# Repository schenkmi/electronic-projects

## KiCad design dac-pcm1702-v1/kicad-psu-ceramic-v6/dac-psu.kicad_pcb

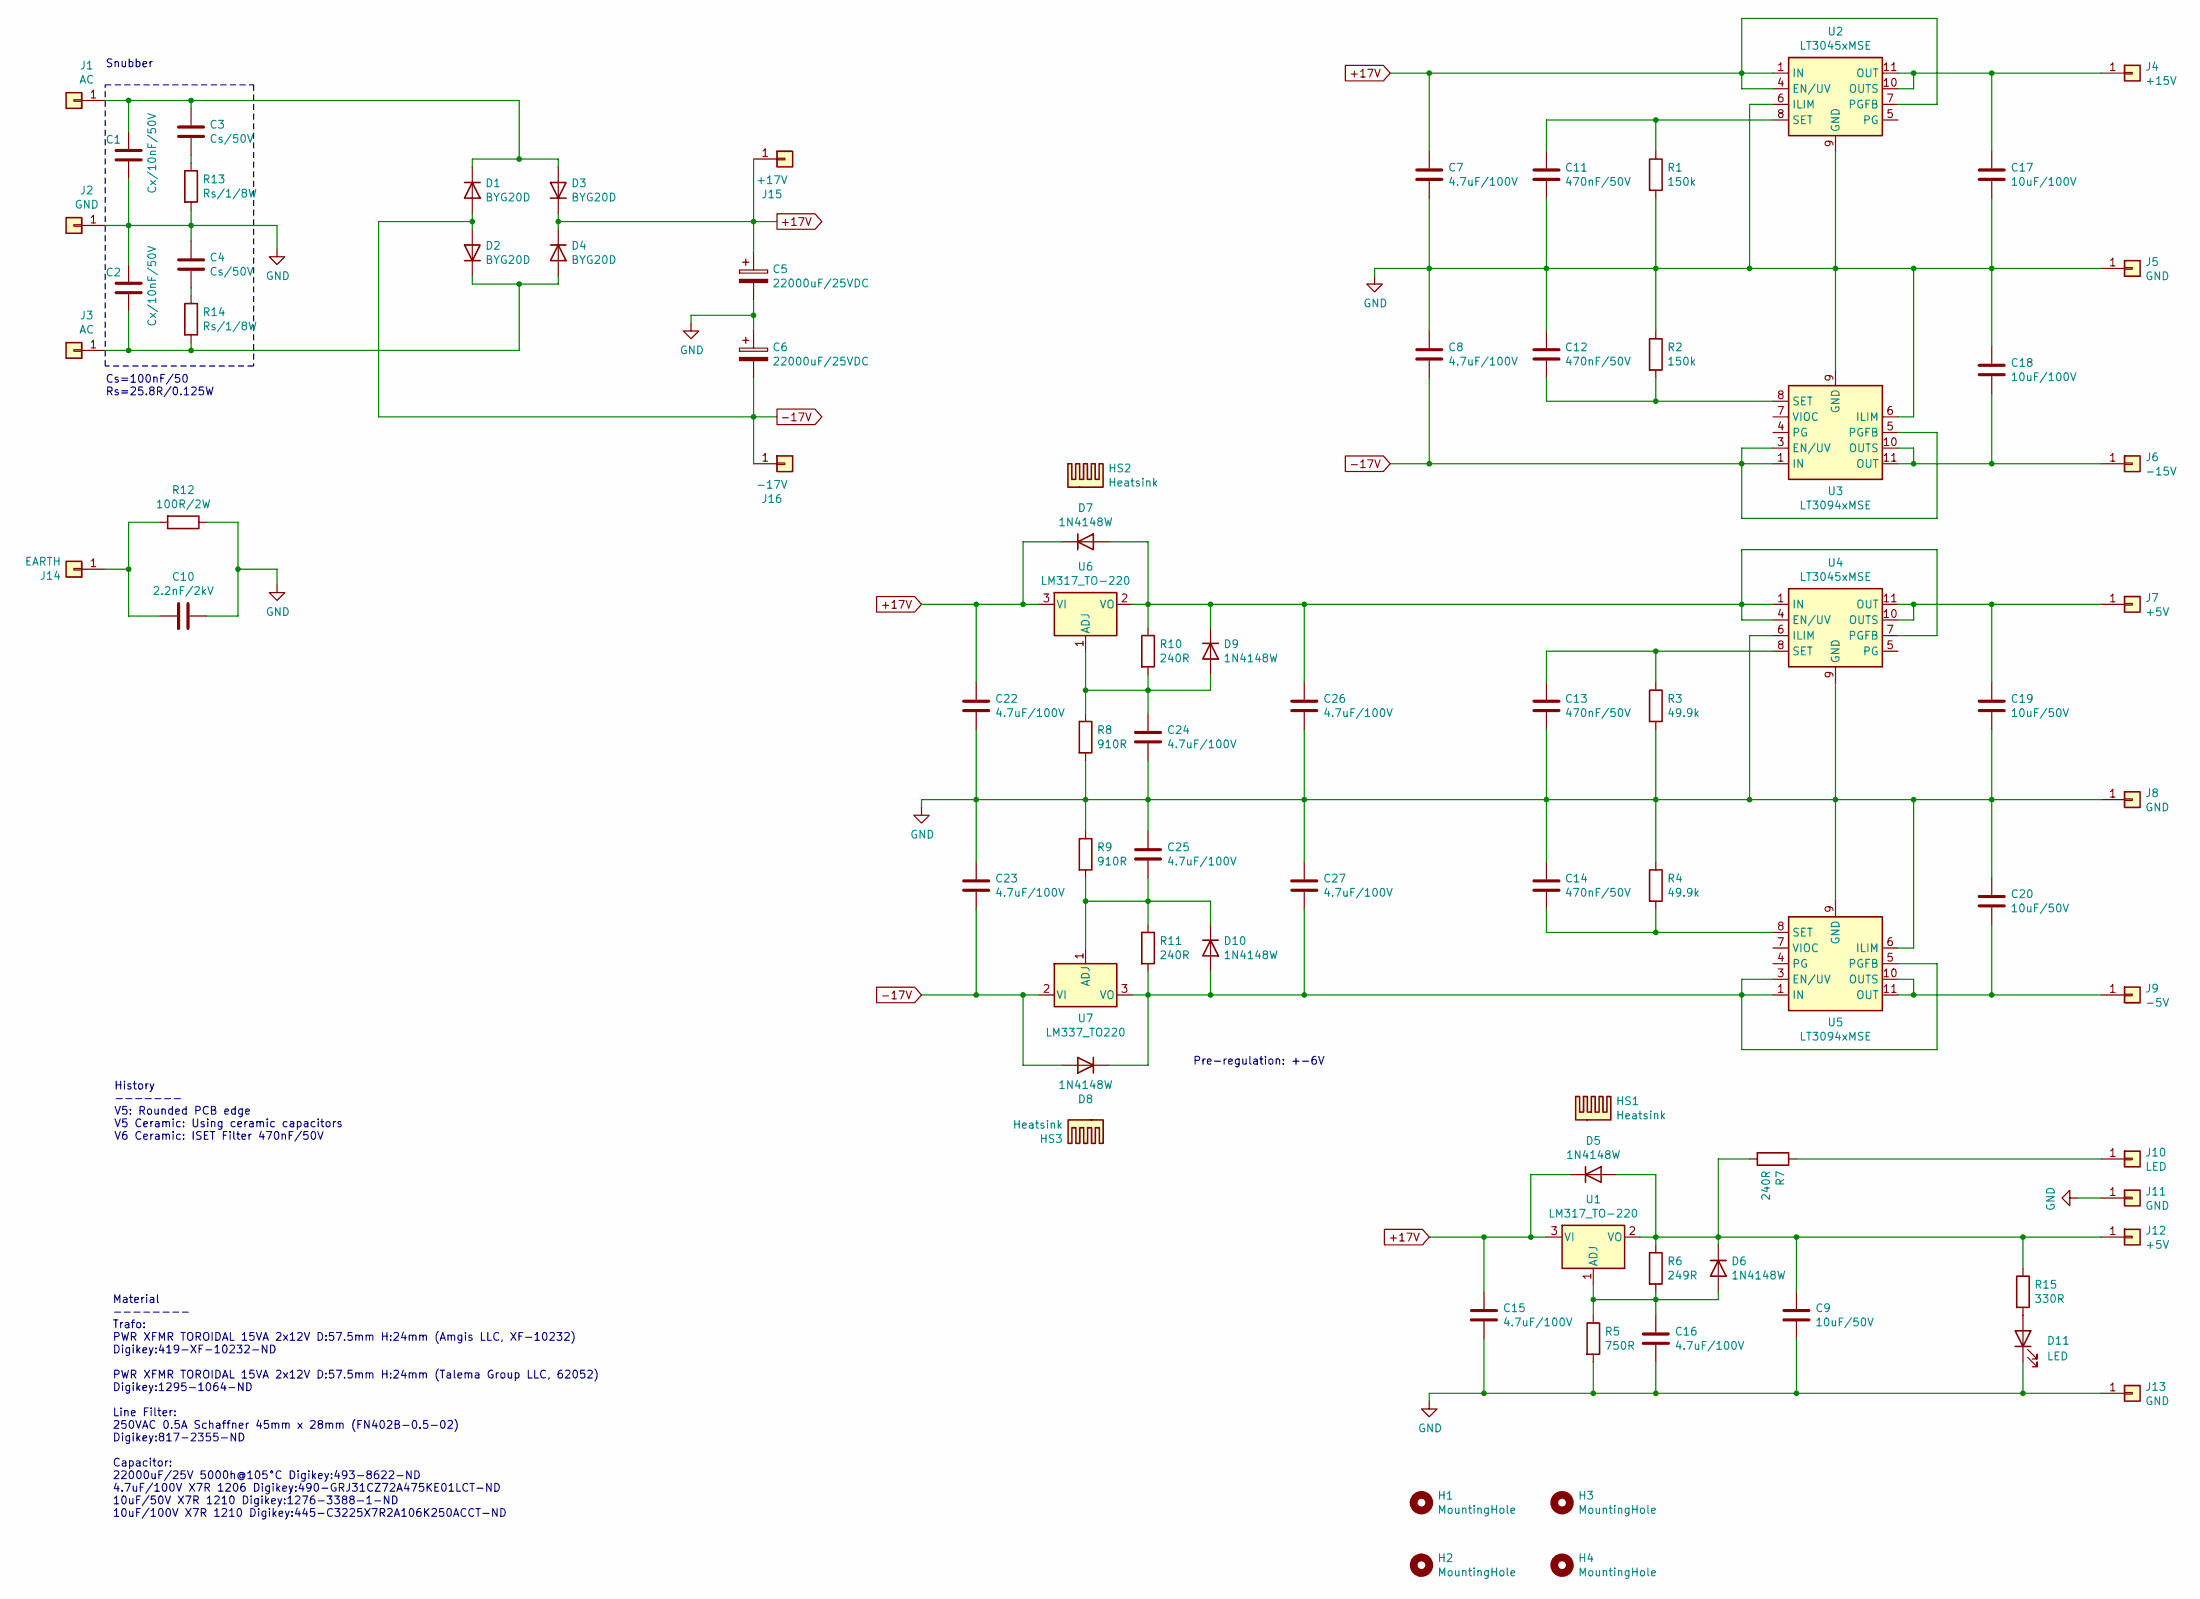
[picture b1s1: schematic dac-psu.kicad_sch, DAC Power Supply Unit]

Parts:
C1, C2: Cx/10nF/50V; C_0805_2012Metric_Pad1.18x1.45mm_HandSolder
C3, C4: Cs/50V; C_0805_2012Metric_Pad1.18x1.45mm_HandSolder
C5, C6: 22000uF/25VDC; CP_Radial_D35.0mm_P10.00mm_SnapIn
C7, C8, C15, C16, C22, C23, C24, C25, C26, C27: 4.7uF/100V; C_1206_3216Metric_Pad1.33x1.80mm_HandSolder
C9, C19, C20: 10uF/50V; C_1210_3225Metric_Pad1.33x2.70mm_HandSolder
C10: 2.2nF/2kV; C_Rect_L18.0mm_W5.0mm_P15.00mm_FKS3_FKP3
C11, C12, C13, C14: 470nF/50V; C_0805_2012Metric_Pad1.18x1.45mm_HandSolder
C17, C18: 10uF/100V; C_1210_3225Metric_Pad1.33x2.70mm_HandSolder
D1, D2, D3, D4: BYG20D; D_SMA_Handsoldering
D5, D6, D7, D8, D9, D10: 1N4148W; D_SOD-123
D11: LED; LED_0805_2012Metric_Pad1.15x1.40mm_HandSolder
H1, H2, H3, H4: MountingHole; MountingHole_3.2mm_M3_Pad_Via
HS1, HS2, HS3: Heatsink; Heatsink_Fischer_SK104-STC-STIC_35x13mm_2xDrill2.5mm
J1, J3: AC; Pin_D1.3mm_L11.0mm
J2: GND; Pin_D1.3mm_L11.0mm
J4: +15V; Pin_D1.0mm_L10.0mm
J5, J8, J11, J13: GND; Pin_D1.0mm_L10.0mm
J6: -15V; Pin_D1.0mm_L10.0mm
J7, J12: +5V; Pin_D1.0mm_L10.0mm
J9: -5V; Pin_D1.0mm_L10.0mm
J10: LED; Pin_D1.0mm_L10.0mm
J14: EARTH; Pin_D1.3mm_L11.0mm
J15: +17V; Pin_D1.3mm_L11.0mm
J16: -17V; Pin_D1.3mm_L11.0mm
R1, R2: 150k; R_0603_1608Metric_Pad0.98x0.95mm_HandSolder
R3, R4: 49.9k; R_0603_1608Metric_Pad0.98x0.95mm_HandSolder
R5: 750R; R_0603_1608Metric_Pad0.98x0.95mm_HandSolder
R6: 249R; R_0603_1608Metric_Pad0.98x0.95mm_HandSolder
R7, R10, R11: 240R; R_0603_1608Metric_Pad0.98x0.95mm_HandSolder
R8, R9: 910R; R_0603_1608Metric_Pad0.98x0.95mm_HandSolder
R12: 100R/2W; R_Axial_DIN0411_L9.9mm_D3.6mm_P15.24mm_Horizontal
R13, R14: Rs/1/8W; R_0805_2012Metric_Pad1.20x1.40mm_HandSolder
R15: 330R; R_0603_1608Metric_Pad0.98x0.95mm_HandSolder
U1, U6: LM317_TO-220; TO-220-3_Vertical
U2, U4: LT3045xMSE; MSOP-12-1EP_3x4.039mm_P0.65mm_EP1.651x2.845mm
U3, U5: LT3094xMSE; MSOP-12-1EP_3x4.039mm_P0.65mm_EP1.651x2.845mm
U7: LM337_TO220; TO-220-3_Vertical

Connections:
+17V: C5.1, C7.1, C15.1, C22.1, D3.1 (K), D4.1 (K), D5.1 (K), D7.1 (K), J15.1, U1.3 (VI), U2.1 (IN), U2.2 (IN), U2.3 (IN), U2.4 (EN/UV), U2.7 (PGFB), U6.3 (VI)
-17V: C6.2, C8.2, C23.2, D1.2 (A), D2.2 (A), D8.2 (A), J16.1, U3.1 (IN), U3.2 (IN), U3.3 (EN/UV), U3.5 (PGFB), U3.13 (IN), U7.2 (VI)
GND: C1.2, C2.1, C4.1, C5.2, C6.1, C7.2, C8.1, C9.2, C10.1, C11.2, C12.1, C13.2, C14.1, C15.2, C16.2, C17.2, C18.1, C19.2, C20.1, C22.2, C23.1, C24.2, C25.1, C26.2, C27.1, D11.1 (K), J2.1, J5.1, J8.1, J11.1, J13.1, R1.2, R2.1, R3.2, R4.1, R5.2, R8.2, R9.1, R12.1, R13.2, U2.6 (ILIM), U2.9 (GND), U2.13 (GND), U3.6 (ILIM), U3.9 (GND), U4.6 (ILIM), U4.9 (GND), U4.13 (GND), U5.6 (ILIM), U5.9 (GND)
unnamed: C3.2, R13.1
unnamed: C4.2, R14.1
unnamed: C1.1, C3.1, D1.1 (K), D3.2 (A), J1.1
unnamed: C2.2, D2.1 (K), D4.2 (A), J3.1, R14.2
unnamed: C9.1, D5.2 (A), D6.1 (K), J12.1, R6.1, R7.2, R15.1, U1.2 (VO)
unnamed: C16.1, D6.2 (A), R5.1, R6.2, U1.1 (ADJ)
unnamed: C26.1, D7.2 (A), D9.1 (K), R10.1, U4.1 (IN), U4.2 (IN), U4.3 (IN), U4.4 (EN/UV), U4.7 (PGFB), U6.2 (VO)
unnamed: C24.1, D9.2 (A), R8.1, R10.2, U6.1 (ADJ)
unnamed: C27.2, D8.1 (K), D10.2 (A), R11.2, U5.1 (IN), U5.2 (IN), U5.3 (EN/UV), U5.5 (PGFB), U5.13 (IN), U7.3 (VO)
unnamed: C25.2, D10.1 (K), R9.2, R11.1, U7.1 (ADJ)
unnamed: D11.2 (A), R15.2
unnamed: C17.1, J4.1, U2.10 (OUTS), U2.11 (OUT), U2.12 (OUT)
unnamed: C18.2, J6.1, U3.10 (OUTS), U3.11 (OUT), U3.12 (OUT)
unnamed: C19.1, J7.1, U4.10 (OUTS), U4.11 (OUT), U4.12 (OUT)
unnamed: C20.2, J9.1, U5.10 (OUTS), U5.11 (OUT), U5.12 (OUT)
unnamed: J10.1, R7.1
unnamed: C10.2, J14.1, R12.2
unnamed: C11.1, R1.1, U2.8 (SET)
unnamed: C12.2, R2.2, U3.8 (SET)
unnamed: C13.1, R3.1, U4.8 (SET)
unnamed: C14.2, R4.2, U5.8 (SET)

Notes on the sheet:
Material -------- Trafo: PWR XFMR TOROIDAL 15VA 2x12V D:57.5mm H:24mm (Amgis LLC, XF-10232) Digikey:419-XF-10232-ND PWR XFMR TOROIDAL 15VA 2x12V D:57.5mm H:24mm (Talema Group LLC, 62052) Digikey:1295-1064-ND Line Filter: 250VAC 0.5A Schaffner 45mm x 28mm (FN402B-0.5-02) Digikey:817-2355-ND Capacito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
Snubber
Cs=100nF/50 Rs=25.8R/0.125W
Pre-regulation: +-6V
History ------- V5: Rounded PCB edge V5 Ceramic: Using ceramic capacitors V6 Ceramic: ISET Filter 470nF/50V

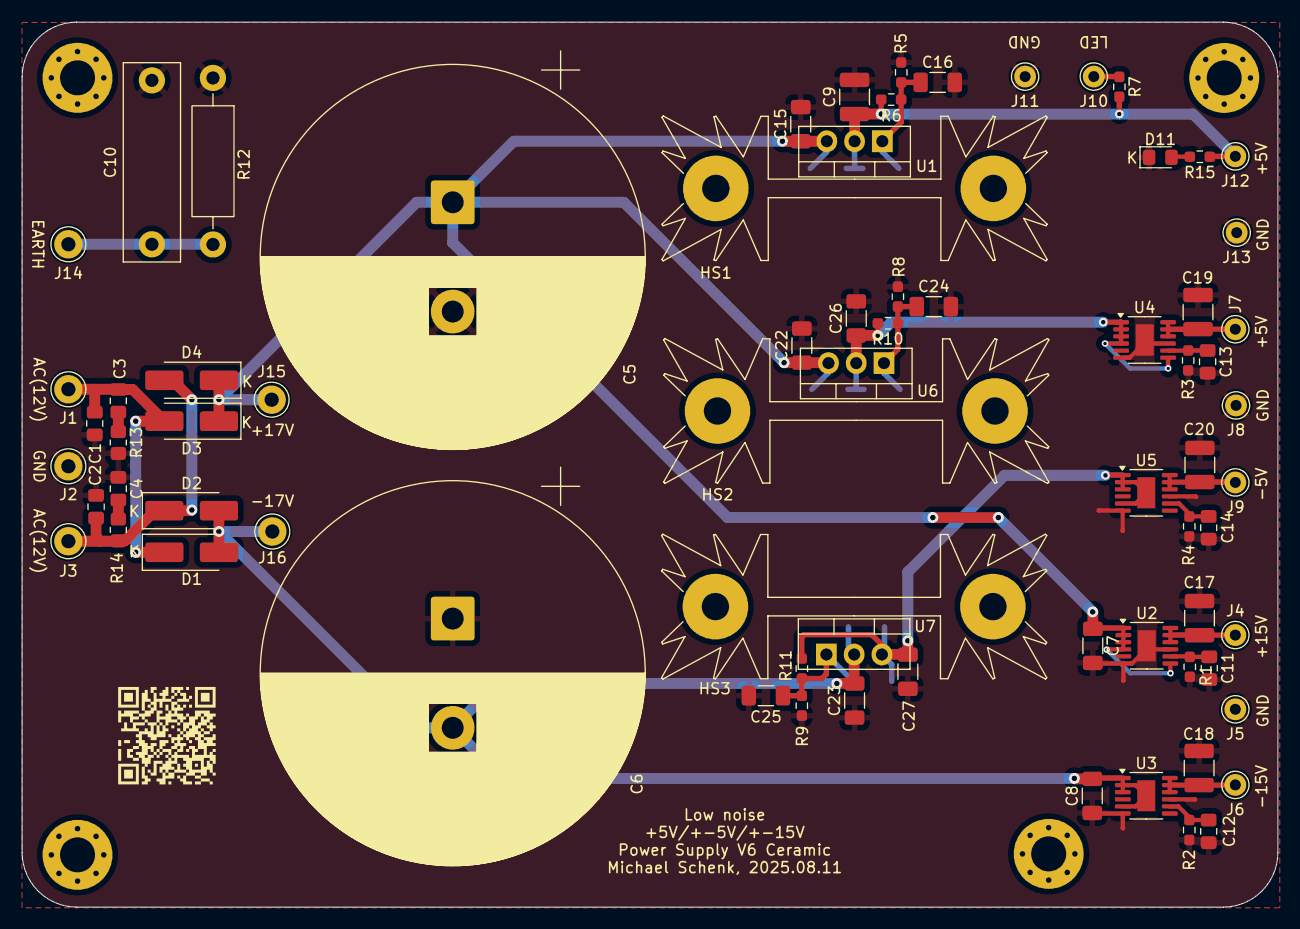
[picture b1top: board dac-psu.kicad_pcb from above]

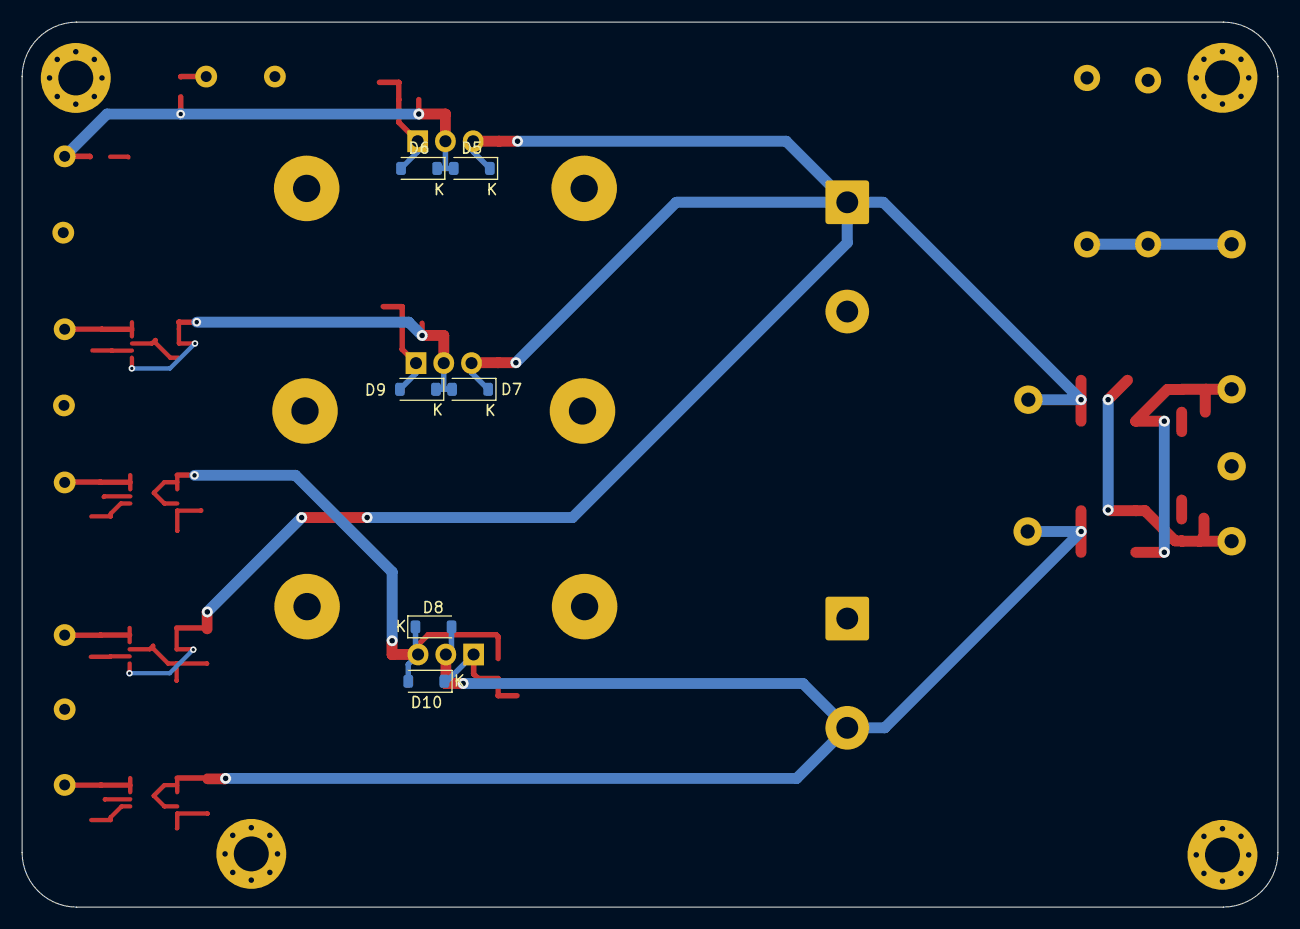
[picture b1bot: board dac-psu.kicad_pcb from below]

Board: 2 copper layers, 114.9 x 81.0 mm, 82 parts (6 on the bottom side), 24 nets.

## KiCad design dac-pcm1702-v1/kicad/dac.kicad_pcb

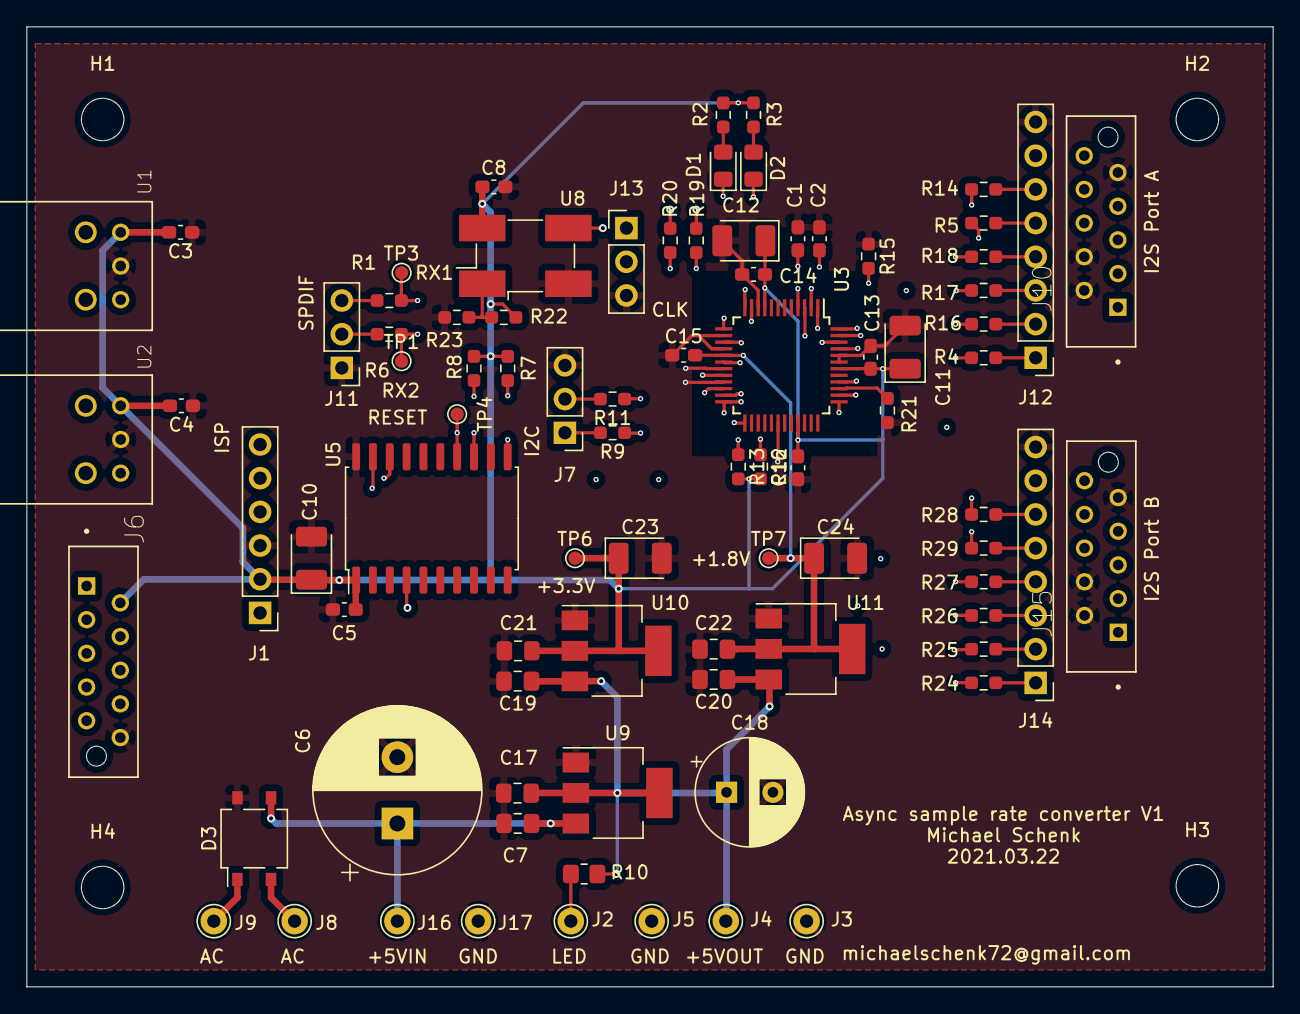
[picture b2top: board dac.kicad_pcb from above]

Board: 4 copper layers, 94.0 x 72.4 mm, 89 parts (0 on the bottom side), 53 nets.

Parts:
C1, C2, C3, C4, C5, C13, C14, C15, C16: 100nF; C_0603_1608Metric_Pad1.08x0.95mm_HandSolder
C6: 1000uF; CP_Radial_D12.5mm_P5.00mm
C7, C19, C20: 330nF; C_0805_2012Metric_Pad1.18x1.45mm_HandSolder
C8: 10nF; C_0603_1608Metric_Pad1.08x0.95mm_HandSolder
C10, C11, C12, C23, C24: 10uF; CP_EIA-3528-21_Kemet-B_Pad1.50x2.35mm_HandSolder
C17, C21, C22: 100nF; C_0805_2012Metric_Pad1.18x1.45mm_HandSolder
C18: 100uF; CP_Radial_D8.0mm_P3.50mm
D1, D2: LED; LED_0805_2012Metric_Pad1.15x1.40mm_HandSolder
D3: MB4S; TO-269AA
H1, H2, H3, H4: MountingHole; MountingHole_3.2mm_M3
J1: Conn_01x06_Male; PinHeader_1x06_P2.54mm_Vertical
J2: LED; Pin_D1.0mm_L10.0mm
J3, J5, J17: GND; Pin_D1.0mm_L10.0mm
J4: +5VOUT; Pin_D1.0mm_L10.0mm
J6: IN; TE_CONN_RCPT_10POS_0.1_TIN_PCB
J7: I2C; PinHeader_1x03_P2.54mm_Vertical
J8, J9: AC; Pin_D1.0mm_L10.0mm
J10: B; TE_CONN_RCPT_10POS_0.1_TIN_PCB
J11: IN; PinHeader_1x03_P2.54mm_Vertical
J12: PORTB; PinHeader_1x08_P2.54mm_Vertical
J13: CLK; PinHeader_1x03_P2.54mm_Vertical
J14: PORTA; PinHeader_1x08_P2.54mm_Vertical
J15: A; TE_CONN_RCPT_10POS_0.1_TIN_PCB
J16: +5VIN; Pin_D1.0mm_L10.0mm
R1, R4, R6, R9, R11, R15, R16, R17, R18, R21, R24, R25, R26, R27: 33R; R_0603_1608Metric_Pad0.98x0.95mm_HandSolder
R2, R3: 330R; R_0603_1608Metric_Pad0.98x0.95mm_HandSolder
R5, R14, R28, R29: 49.9R; R_0603_1608Metric_Pad0.98x0.95mm_HandSolder
R7, R8, R22, R23: 4K99; R_0603_1608Metric_Pad0.98x0.95mm_HandSolder
R10: 330R; R_0805_2012Metric_Pad1.20x1.40mm_HandSolder
R12: 1k; R_0603_1608Metric_Pad0.98x0.95mm_HandSolder
R13: 4k99; R_0603_1608Metric_Pad0.98x0.95mm_HandSolder
R19, R20: 0R; R_0603_1608Metric_Pad0.98x0.95mm_HandSolder
TP1: RX2+; TestPoint_Pad_D1.0mm
TP3: RX1+; TestPoint_Pad_D1.0mm
TP4: RESET; TestPoint_Pad_D1.0mm
TP6: 3.3V; TestPoint_Pad_D1.0mm
TP7: 1.8V; TestPoint_Pad_D1.0mm
U1, U2: PLR135-T10; PLR135-T10_PLT133-T10W
U3: SRC4392; TQFP-48_7x7mm_P0.5mm
U5: PIC16F1829-IP; SOIC-20W_7.5x12.8mm_P1.27mm
U8: ASDMB-xxxMHz; Oscillator_SMD_EuroQuartz_XO91-4Pin_7.0x5.0mm_HandSoldering
U9: TLV1117-50; SOT-223-3_TabPin2
U10: TLV1117-33; SOT-223-3_TabPin2
U11: TLV1117-18; SOT-223-3_TabPin2

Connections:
+1V8: C15.2, C22.1, C24.1, TP7.1, U3.17, U11.2
+3V3: C3.2, C4.2, C5.2, C8.1, C10.1, C11.1, C12.1, C13.2, C14.2, C16.2, C21.1, C23.1, J1.2, J6.2, R2.1, R3.1, R7.1, R8.1, R12.2, R13.2, R22.2, TP6.1, U1.1, U2.1, U3.9, U3.33, U3.42, U5.1, U8.4, U10.2
BCKA: R25.2, U3.37
BCKB: R16.2, U3.48
GND: C1.1, C2.2, C3.1, C4.1, C5.1, C6.2, C7.2, C8.2, C10.2, C11.2, C12.2, C13.1, C14.1, C15.1, C16.1, C17.2, C18.2, C19.2, C20.2, C21.2, C22.2, C23.2, C24.2, D3.4, J1.3, J3.1, J5.1, J6.10, J7.3, J10.2, J10.4, J10.9, J11.1, J12.8, J13.3, J14.8, J15.2, J15.4, J15.9, J17.1, R15.1, R21.1, R23.1, U1.2, U2.2, U3.10, U3.14, U3.16, U3.19, U3.21, U3.30, U3.43, U3.44, U5.20, U8.2, U9.1, U10.1, U11.1
LRCKA: R26.2, U3.38
LRCKB: R17.2, U3.47
MCLK: R4.2, R20.1, R24.2, U3.25
unnamed: C1.2, U3.4
unnamed: C2.1, U3.2
unnamed: C6.1, C7.1, D3.3, J16.1, U9.3
unnamed: C17.1, C18.1, C19.1, C20.1, J4.1, R10.2, U9.2, U10.3, U11.3
unnamed: D1.1, U3.15
unnamed: D1.2, R2.2
unnamed: D2.1, U3.11
unnamed: D2.2, R3.2
unnamed: D3.1, J9.1
unnamed: D3.2, J8.1
unnamed: J1.1, U5.4
unnamed: J1.4, U5.19
unnamed: J1.5, U5.18
unnamed: J2.1, R10.1
unnamed: J10.1, J12.1, R4.1
unnamed: J10.3, J12.2, R16.1
unnamed: J10.5, J12.3, R17.1
unnamed: J10.6, J12.5, R5.2
unnamed: J10.7, J12.4, R18.1
unnamed: J10.8, J12.6, R14.2
unnamed: J6.6, J11.2, R6.2, U2.3
unnamed: J6.4, J11.3, R1.2, U1.3
unnamed: J13.1, R19.2, R20.2, U8.3
unnamed: J13.2, U3.12
unnamed: J14.1, J15.1, R24.1
unnamed: J14.2, J15.3, R25.1
unnamed: J14.3, J15.5, R26.1
unnamed: J14.4, J15.7, R27.1
unnamed: J14.5, J15.6, R29.2
unnamed: J14.6, J15.8, R28.2
unnamed: R1.1, TP3.1, U3.1
unnamed: R6.1, TP1.1, U3.3
unnamed: R9.1, U3.22
unnamed: R11.1, U3.20
unnamed: R12.1, U3.18
unnamed: R13.1, U3.23
unnamed: R15.2, U3.46
unnamed: R19.1, U3.13
unnamed: R21.2, U3.39
unnamed: R22.1, R23.2, U8.1
RESET: J10.10, J12.7, J14.7, J15.10, TP4.1, U3.24, U5.14
SCL: J7.2, R7.2, R11.2, R14.1, R28.1, U5.11
SDA: J7.1, R5.1, R8.2, R9.2, R29.1, U5.13
SDOUTA: R27.2, U3.40
SDOUTB: R18.2, U3.45
